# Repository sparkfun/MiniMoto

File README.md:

**NOTE:** *This product has been retired from our catalog. If you are looking for more up-to-date info, please check out some of these resources to see how other users are still hacking and improving on this product.*
* *[SparkFun Forum](https://forum.sparkfun.com/)*
* *[Comments Here on GitHub](https://github.com/sparkfun/MiniMoto/issues)*
* *[IRC Channel](https://www.sparkfun.com/news/263)*

SparkFun MiniMoto Breakout - DRV8830
=========================================

[*SparkFun MiniMoto Breakout - DRV8830(BOB-11890)*](https://www.sparkfun.com/products/11890)

The MiniMoto is a breakout board for the DRV8830 I<sup>2</sup>C DC motor driver. It operates between 2.7V to 6.8V

Repository Contents
-------------------
* **/Hardware** - All Eagle design files (.brd, .sch)
* **/Libraries** - All Arduino libraries and board examples
* **/Production** - Test bed files and production panel files

Documentation
--------------
* **[Library](https://github.com/sparkfun/SparkFun_MiniMoto_Arduino_Library)** - Arduinolibrary for the MiniMoto.
* **[Hookup Guide](https://learn.sparkfun.com/tutorials/minimoto-drv8830-hookup-guide)** - Basic hookup guide for the MiniMoto.
* **[SparkFun Fritzing repo](https://github.com/sparkfun/Fritzing_Parts)** - Fritzing diagrams for SparkFun products.
* **[SparkFun 3D Model repo](https://github.com/sparkfun/3D_Models)** - 3D models of SparkFun products. 

License Information
-------------------
This product is _**open source**_! 

The **hardware** is released under [Creative Commons ShareAlike 4.0 International](https://creativecommons.org/licenses/by-sa/4.0/).

The **code** is beerware; if you see me (or any other SparkFun employee) at the local, and you've found our code helpful, please buy us a round!

Please use, reuse, and modify these files as you see fit. Please maintain attribution to SparkFun Electronics and release anything derivative under the same license.

Distributed as-is; no warranty is given.

- Your friends at SparkFun.

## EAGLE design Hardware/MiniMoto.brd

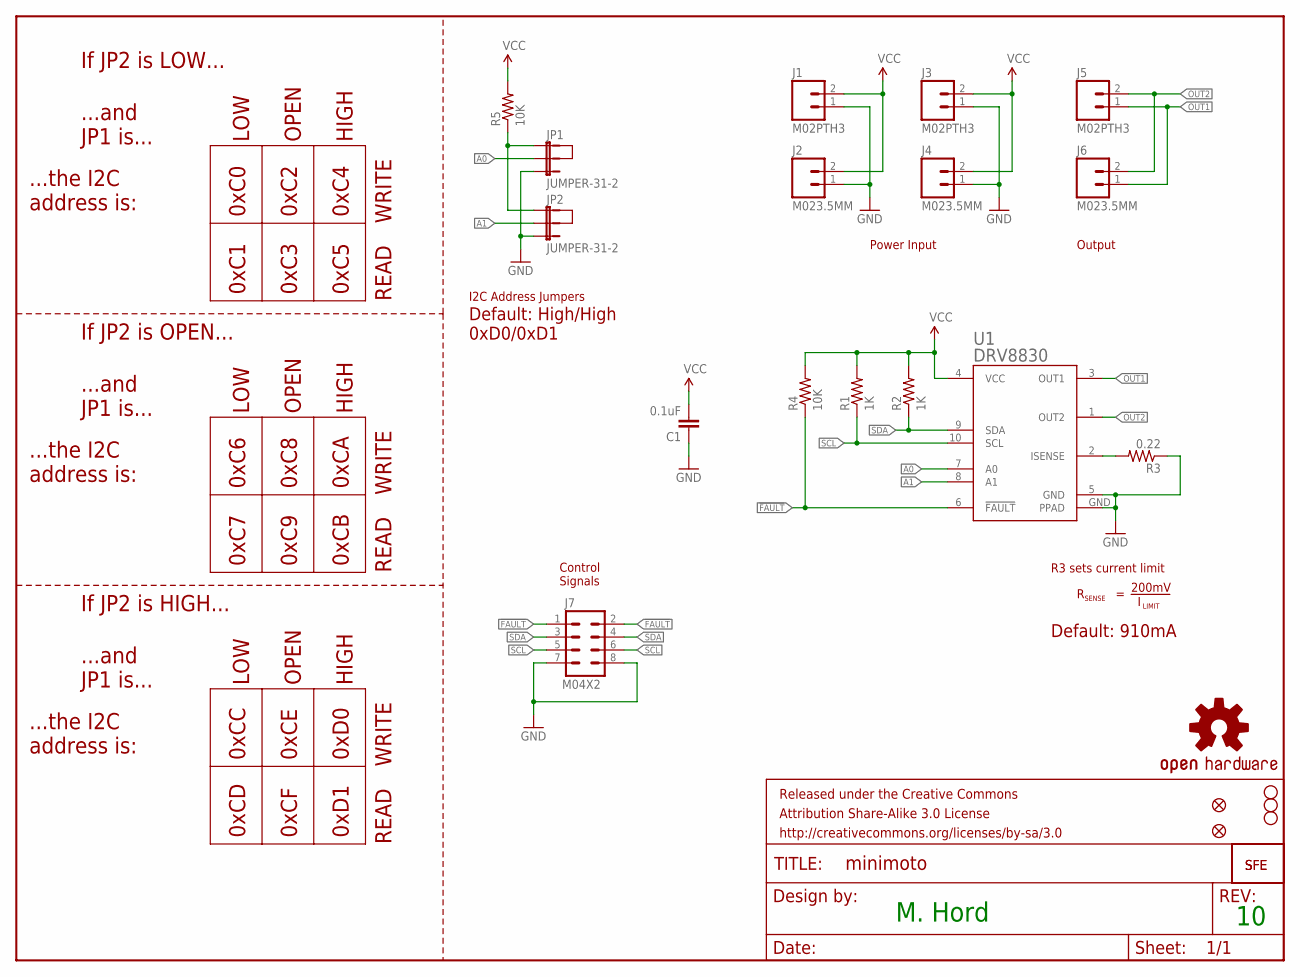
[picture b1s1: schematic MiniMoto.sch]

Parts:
C1: 0.1uF; 0603-CAP
FID1, FID2: FIDUCIALUFIDUCIAL; MICRO-FIDUCIAL
FRAME1: FRAME-LETTER; CREATIVE_COMMONS
J1, J3, J5: M02PTH3; 1X02_LONGPADS
J2, J4, J6: M023.5MM; SCREWTERMINAL-3.5MM-2
J7: M04X2; 2X4
JP1, JP2: JUMPER-31-2; SJ_3_PASTE1&2
LOGO1, LOGO3: LOGO-SFESK; SFE-LOGO-FLAME
LOGO2: OSHW-LOGOS; OSHW-LOGO-S
R1, R2: 1K; 0603-RES
R3: 0.22; 0805
R4, R5: 10K; 0603-RES
STANDOFF1, STANDOFF2, STANDOFF3: STAND-OFF
U1: DRV8830; MSOP-10-GNDPAD

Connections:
!FAULT: J7.1, J7.2, R4.1, U1.6 (!FAULT)
A0: JP1.2, U1.7 (A0)
A1: JP2.2, U1.8 (A1)
GND: C1.1, J1.1, J2.1, J3.1, J4.1, J7.7, J7.8, JP1.3, JP2.3, R3.1, U1.5 (GND), U1.GND (PPAD)
unnamed: JP1.1, JP2.1, R5.1
unnamed: R3.2, U1.2 (ISENSE)
OUT1: J5.1, J6.1, U1.3 (OUT1)
OUT2: J5.2, J6.2, U1.1 (OUT2)
SCL: J7.5, J7.6, R1.1, U1.10 (SCL)
SDA: J7.3, J7.4, R2.1, U1.9 (SDA)
VCC: C1.2, J1.2, J2.2, J3.2, J4.2, R1.2, R2.2, R4.2, R5.2, U1.4 (VCC)

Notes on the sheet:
M. Hord
If JP2 is LOW...
HIGH
LOW
OPEN
...and JP1 is...
...the I2C address is:
0xC0
0xC2
0xC4
0xC1
0xC3
0xC5
WRITE
READ
If JP2 is OPEN...
0xC6
0xC8
0xCA
0xC7
0xC9
0xCB
If JP2 is HIGH...
0xCC
0xCE
0xD0
0xCD
0xCF
0xD1
R3 sets current limit
SENSE
200mV
LIMIT
Control Signals
Power Input
Output
I2C Address Jumpers
Default: High/High 0xD0/0xD1
Default: 910mA

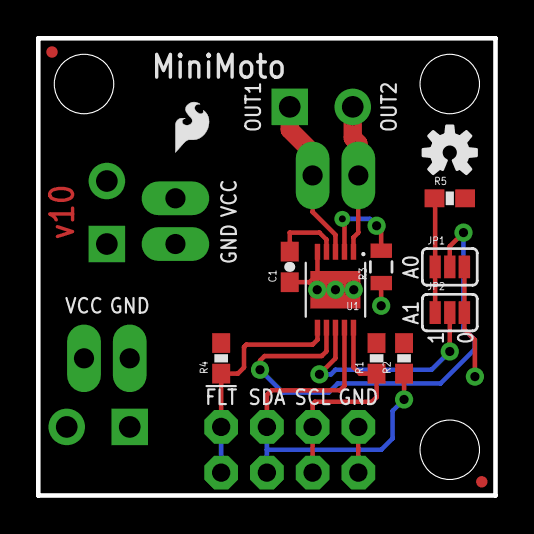
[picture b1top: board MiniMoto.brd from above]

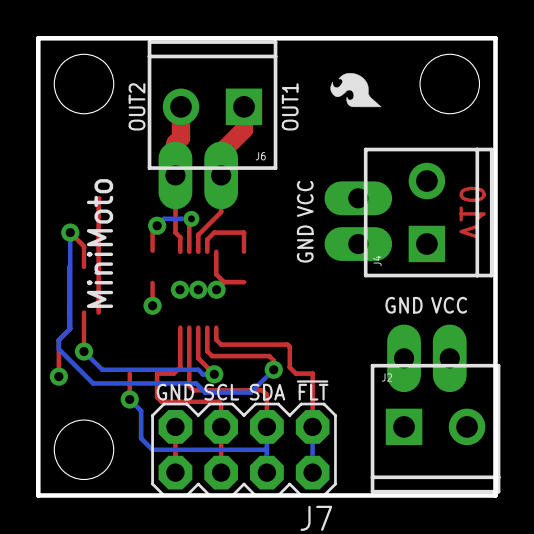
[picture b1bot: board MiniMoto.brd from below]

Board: 2 copper layers, 25.4 x 25.4 mm, 25 parts (7 on the bottom side), 11 nets.

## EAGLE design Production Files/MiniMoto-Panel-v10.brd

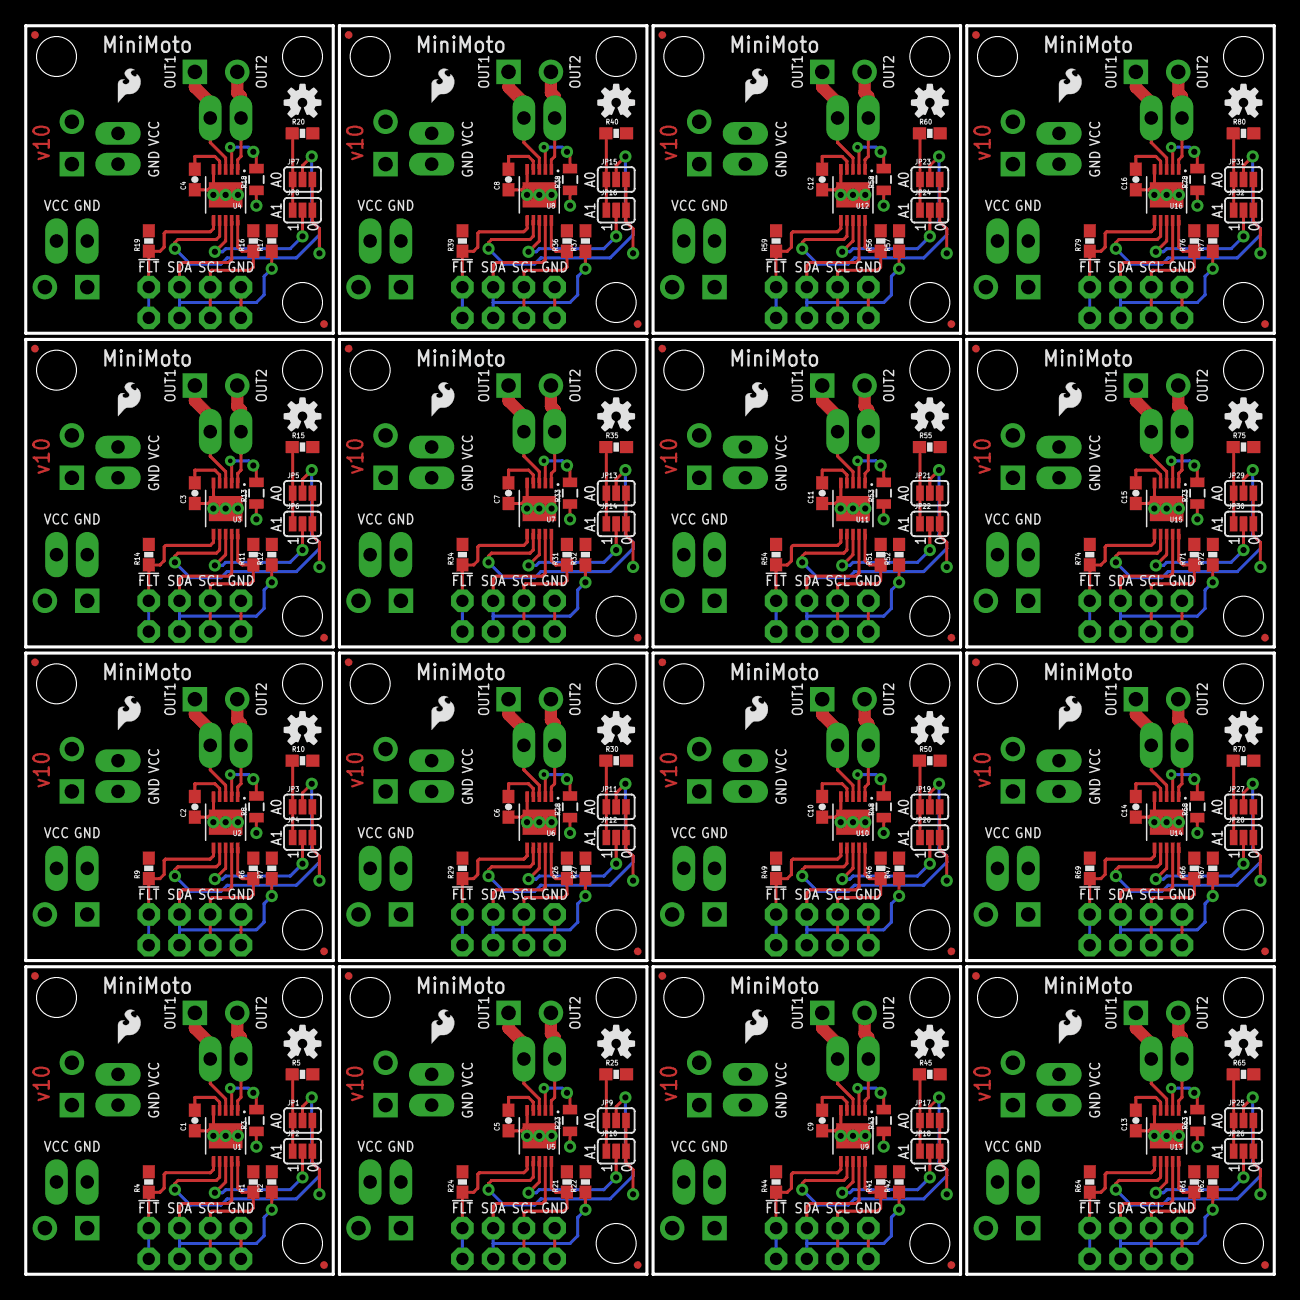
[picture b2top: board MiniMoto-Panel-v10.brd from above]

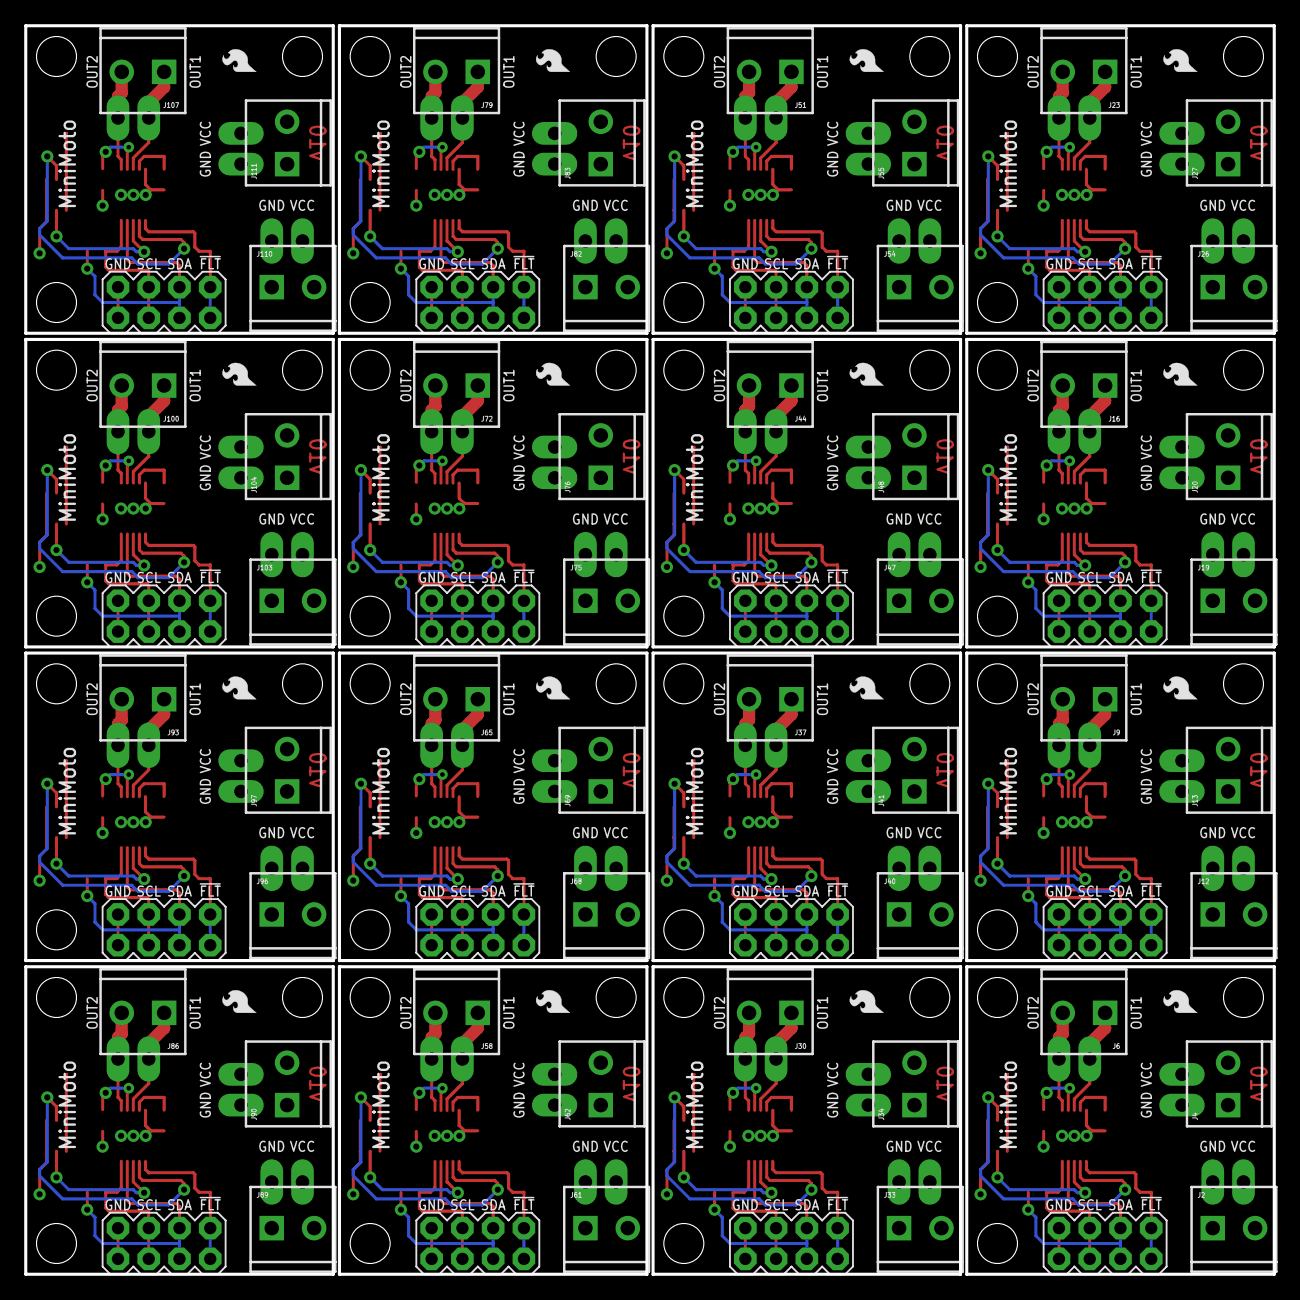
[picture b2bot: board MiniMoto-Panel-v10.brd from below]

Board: 2 copper layers, 103.1 x 103.1 mm, 384 parts (112 on the bottom side), 176 nets.

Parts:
C1, C2, C3, C4, C5, C6, C7, C8, C9, C10, C11, C12, C13, C14, C15, C16: 0.1uF; 0603-CAP
FID1, FID2, FID3, FID4, FID5, FID6, FID7, FID8, FID9, FID10, FID11, FID12, FID13, FID14, FID15, FID16, FID17, FID18, FID19, FID20, FID21, FID22, FID23, FID24, FID25, FID26, FID27, FID28, FID29, FID30, FID31, FID32: FIDUCIALUFIDUCIAL; MICRO-FIDUCIAL
J1, J3, J5, J8, J11, J14, J15, J18, J21, J22, J25, J28, J29, J32, J35, J36, J39, J42, J43, J46, J49, J50, J53, J56, J57, J60, J63, J64, J67, J70, J71, J74, J77, J78, J81, J84, J85, J88, J91, J92, J95, J98, J99, J102, J105, J106, J109, J112: M02PTH3; 1X02_LONGPADS
J2, J4, J6, J9, J12, J13, J16, J19, J20, J23, J26, J27, J30, J33, J34, J37, J40, J41, J44, J47, J48, J51, J54, J55, J58, J61, J62, J65, J68, J69, J72, J75, J76, J79, J82, J83, J86, J89, J90, J93, J96, J97, J100, J103, J104, J107, J110, J111: M023.5MM; SCREWTERMINAL-3.5MM-2
J7, J10, J17, J24, J31, J38, J45, J52, J59, J66, J73, J80, J87, J94, J101, J108: M04X2; 2X4
JP1, JP2, JP3, JP4, JP5, JP6, JP7, JP8, JP9, JP10, JP11, JP12, JP13, JP14, JP15, JP16, JP17, JP18, JP19, JP20, JP21, JP22, JP23, JP24, JP25, JP26, JP27, JP28, JP29, JP30, JP31, JP32: JUMPER-31-2; SJ_3_PASTE1&2
LOGO1, LOGO3, LOGO5, LOGO6, LOGO8, LOGO9, LOGO11, LOGO12, LOGO14, LOGO15, LOGO17, LOGO18, LOGO20, LOGO21, LOGO23, LOGO24, LOGO26, LOGO27, LOGO29, LOGO30, LOGO32, LOGO33, LOGO35, LOGO36, LOGO38, LOGO39, LOGO41, LOGO42, LOGO44, LOGO45, LOGO47, LOGO48: LOGO-SFESK; SFE-LOGO-FLAME
LOGO2, LOGO4, LOGO7, LOGO10, LOGO13, LOGO16, LOGO19, LOGO22, LOGO25, LOGO28, LOGO31, LOGO34, LOGO37, LOGO40, LOGO43, LOGO46: OSHW-LOGOS; OSHW-LOGO-S
R1, R2, R6, R7, R11, R12, R16, R17, R21, R22, R26, R27, R31, R32, R36, R37, R41, R42, R46, R47, R51, R52, R56, R57, R61, R62, R66, R67, R71, R72, R76, R77: 1K; 0603-RES
R3, R8, R13, R18, R23, R28, R33, R38, R43, R48, R53, R58, R63, R68, R73, R78: 0.22; 0805
R4, R5, R9, R10, R14, R15, R19, R20, R24, R25, R29, R30, R34, R35, R39, R40, R44, R45, R49, R50, R54, R55, R59, R60, R64, R65, R69, R70, R74, R75, R79, R80: 10K; 0603-RES
STANDOFF1, STANDOFF2, STANDOFF3, STANDOFF4, STANDOFF5, STANDOFF6, STANDOFF7, STANDOFF8, STANDOFF9, STANDOFF10, STANDOFF11, STANDOFF12, STANDOFF13, STANDOFF14, STANDOFF15, STANDOFF16, STANDOFF17, STANDOFF18, STANDOFF19, STANDOFF20, STANDOFF21, STANDOFF22, STANDOFF23, STANDOFF24, STANDOFF25, STANDOFF26, STANDOFF27, STANDOFF28, STANDOFF29, STANDOFF30, STANDOFF31, STANDOFF32, STANDOFF33, STANDOFF34, STANDOFF35, STANDOFF36, STANDOFF37, STANDOFF38, STANDOFF39, STANDOFF40, STANDOFF41, STANDOFF42, STANDOFF43, STANDOFF44, STANDOFF45, STANDOFF46, STANDOFF47, STANDOFF48: STAND-OFF
U1, U2, U3, U4, U5, U6, U7, U8, U9, U10, U11, U12, U13, U14, U15, U16: DRV8830; MSOP-10-GNDPAD

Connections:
!FAULT: J7.1, J7.2, R4.1, U1.6
!FAULT1: J10.1, J10.2, R9.1, U2.6
!FAULT2: J17.1, J17.2, R14.1, U3.6
!FAULT3: J24.1, J24.2, R19.1, U4.6
!FAULT4: J31.1, J31.2, R24.1, U5.6
!FAULT5: J38.1, J38.2, R29.1, U6.6
!FAULT6: J45.1, J45.2, R34.1, U7.6
!FAULT7: J52.1, J52.2, R39.1, U8.6
!FAULT8: J59.1, J59.2, R44.1, U9.6
!FAULT9: J66.1, J66.2, R49.1, U10.6
!FAULT10: J73.1, J73.2, R54.1, U11.6
!FAULT11: J80.1, J80.2, R59.1, U12.6
!FAULT12: J87.1, J87.2, R64.1, U13.6
!FAULT13: J94.1, J94.2, R69.1, U14.6
!FAULT14: J101.1, J101.2, R74.1, U15.6
!FAULT15: J108.1, J108.2, R79.1, U16.6
A0: JP1.2, U1.7
A1: JP2.2, U1.8
A2: JP3.2, U2.7
A3: JP4.2, U2.8
A4: JP5.2, U3.7
A5: JP6.2, U3.8
A6: JP7.2, U4.7
A7: JP8.2, U4.8
A8: JP9.2, U5.7
A9: JP10.2, U5.8
A10: JP11.2, U6.7
A11: JP12.2, U6.8
A12: JP13.2, U7.7
A13: JP14.2, U7.8
A14: JP15.2, U8.7
A15: JP16.2, U8.8
A16: JP17.2, U9.7
A17: JP18.2, U9.8
A18: JP19.2, U10.7
A19: JP20.2, U10.8
A20: JP21.2, U11.7
A21: JP22.2, U11.8
A22: JP23.2, U12.7
A23: JP24.2, U12.8
A24: JP25.2, U13.7
A25: JP26.2, U13.8
A26: JP27.2, U14.7
A27: JP28.2, U14.8
A28: JP29.2, U15.7
A29: JP30.2, U15.8
A30: JP31.2, U16.7
A31: JP32.2, U16.8
GND: C1.1, J1.1, J2.1, J3.1, J4.1, J7.7, J7.8, JP1.3, JP2.3, R3.1, U1.5, U1.GND
GND1: C2.1, J10.7, J10.8, J11.1, J12.1, J13.1, J14.1, JP3.3, JP4.3, R8.1, U2.5, U2.GND
GND2: C3.1, J17.7, J17.8, J18.1, J19.1, J20.1, J21.1, JP5.3, JP6.3, R13.1, U3.5, U3.GND
GND3: C4.1, J24.7, J24.8, J25.1, J26.1, J27.1, J28.1, JP7.3, JP8.3, R18.1, U4.5, U4.GND
GND4: C5.1, J31.7, J31.8, J32.1, J33.1, J34.1, J35.1, JP9.3, JP10.3, R23.1, U5.5, U5.GND
GND5: C6.1, J38.7, J38.8, J39.1, J40.1, J41.1, J42.1, JP11.3, JP12.3, R28.1, U6.5, U6.GND
GND6: C7.1, J45.7, J45.8, J46.1, J47.1, J48.1, J49.1, JP13.3, JP14.3, R33.1, U7.5, U7.GND
GND7: C8.1, J52.7, J52.8, J53.1, J54.1, J55.1, J56.1, JP15.3, JP16.3, R38.1, U8.5, U8.GND
GND8: C9.1, J59.7, J59.8, J60.1, J61.1, J62.1, J63.1, JP17.3, JP18.3, R43.1, U9.5, U9.GND
GND9: C10.1, J66.7, J66.8, J67.1, J68.1, J69.1, J70.1, JP19.3, JP20.3, R48.1, U10.5, U10.GND
GND10: C11.1, J73.7, J73.8, J74.1, J75.1, J76.1, J77.1, JP21.3, JP22.3, R53.1, U11.5, U11.GND
GND11: C12.1, J80.7, J80.8, J81.1, J82.1, J83.1, J84.1, JP23.3, JP24.3, R58.1, U12.5, U12.GND
GND12: C13.1, J87.7, J87.8, J88.1, J89.1, J90.1, J91.1, JP25.3, JP26.3, R63.1, U13.5, U13.GND
GND13: C14.1, J94.7, J94.8, J95.1, J96.1, J97.1, J98.1, JP27.3, JP28.3, R68.1, U14.5, U14.GND
GND14: C15.1, J101.7, J101.8, J102.1, J103.1, J104.1, J105.1, JP29.3, JP30.3, R73.1, U15.5, U15.GND
GND15: C16.1, J108.7, J108.8, J109.1, J110.1, J111.1, J112.1, JP31.3, JP32.3, R78.1, U16.5, U16.GND
unnamed: JP1.1, JP2.1, R5.1
unnamed: R8.2, U2.2
unnamed: R3.2, U1.2
unnamed: JP3.1, JP4.1, R10.1
unnamed: R13.2, U3.2
unnamed: JP5.1, JP6.1, R15.1
unnamed: R18.2, U4.2
unnamed: JP7.1, JP8.1, R20.1
unnamed: R23.2, U5.2
unnamed: JP9.1, JP10.1, R25.1
unnamed: R28.2, U6.2
unnamed: JP11.1, JP12.1, R30.1
unnamed: R33.2, U7.2
unnamed: JP13.1, JP14.1, R35.1
unnamed: R38.2, U8.2
unnamed: JP15.1, JP16.1, R40.1
unnamed: R43.2, U9.2
unnamed: JP17.1, JP18.1, R45.1
unnamed: R48.2, U10.2
unnamed: JP19.1, JP20.1, R50.1
unnamed: R53.2, U11.2
unnamed: JP21.1, JP22.1, R55.1
unnamed: R58.2, U12.2
unnamed: JP23.1, JP24.1, R60.1
unnamed: R63.2, U13.2
unnamed: JP25.1, JP26.1, R65.1
unnamed: R68.2, U14.2
unnamed: JP27.1, JP28.1, R70.1
unnamed: R73.2, U15.2
unnamed: JP29.1, JP30.1, R75.1
unnamed: R78.2, U16.2
unnamed: JP31.1, JP32.1, R80.1
OUT1: J5.1, J6.1, U1.3
OUT2: J5.2, J6.2, U1.1
OUT3: J8.1, J9.1, U2.3
OUT4: J8.2, J9.2, U2.1
OUT5: J15.1, J16.1, U3.3
OUT6: J15.2, J16.2, U3.1
OUT7: J22.1, J23.1, U4.3
OUT8: J22.2, J23.2, U4.1
OUT9: J29.1, J30.1, U5.3
OUT10: J29.2, J30.2, U5.1
OUT11: J36.1, J37.1, U6.3
OUT12: J36.2, J37.2, U6.1
OUT13: J43.1, J44.1, U7.3
OUT14: J43.2, J44.2, U7.1
OUT15: J50.1, J51.1, U8.3
OUT16: J50.2, J51.2, U8.1
OUT17: J57.1, J58.1, U9.3
OUT18: J57.2, J58.2, U9.1
OUT19: J64.1, J65.1, U10.3
OUT20: J64.2, J65.2, U10.1
OUT21: J71.1, J72.1, U11.3
OUT22: J71.2, J72.2, U11.1
OUT23: J78.1, J79.1, U12.3
OUT24: J78.2, J79.2, U12.1
OUT25: J85.1, J86.1, U13.3
OUT26: J85.2, J86.2, U13.1
OUT27: J92.1, J93.1, U14.3
OUT28: J92.2, J93.2, U14.1
OUT29: J99.1, J100.1, U15.3
OUT30: J99.2, J100.2, U15.1
OUT31: J106.1, J107.1, U16.3
OUT32: J106.2, J107.2, U16.1
SCL: J7.5, J7.6, R1.1, U1.10
SCL1: J10.5, J10.6, R6.1, U2.10
SCL2: J17.5, J17.6, R11.1, U3.10
SCL3: J24.5, J24.6, R16.1, U4.10
SCL4: J31.5, J31.6, R21.1, U5.10
SCL5: J38.5, J38.6, R26.1, U6.10
SCL6: J45.5, J45.6, R31.1, U7.10
SCL7: J52.5, J52.6, R36.1, U8.10
SCL8: J59.5, J59.6, R41.1, U9.10
SCL9: J66.5, J66.6, R46.1, U10.10
SCL10: J73.5, J73.6, R51.1, U11.10
SCL11: J80.5, J80.6, R56.1, U12.10
SCL12: J87.5, J87.6, R61.1, U13.10
SCL13: J94.5, J94.6, R66.1, U14.10
SCL14: J101.5, J101.6, R71.1, U15.10
SCL15: J108.5, J108.6, R76.1, U16.10
SDA: J7.3, J7.4, R2.1, U1.9
SDA1: J10.3, J10.4, R7.1, U2.9
SDA2: J17.3, J17.4, R12.1, U3.9
SDA3: J24.3, J24.4, R17.1, U4.9
SDA4: J31.3, J31.4, R22.1, U5.9
SDA5: J38.3, J38.4, R27.1, U6.9
SDA6: J45.3, J45.4, R32.1, U7.9
SDA7: J52.3, J52.4, R37.1, U8.9
SDA8: J59.3, J59.4, R42.1, U9.9
SDA9: J66.3, J66.4, R47.1, U10.9
SDA10: J73.3, J73.4, R52.1, U11.9
SDA11: J80.3, J80.4, R57.1, U12.9
SDA12: J87.3, J87.4, R62.1, U13.9
SDA13: J94.3, J94.4, R67.1, U14.9
SDA14: J101.3, J101.4, R72.1, U15.9
SDA15: J108.3, J108.4, R77.1, U16.9
VCC: C1.2, J1.2, J2.2, J3.2, J4.2, R1.2, R2.2, R4.2, R5.2, U1.4
VCC1: C2.2, J11.2, J12.2, J13.2, J14.2, R6.2, R7.2, R9.2, R10.2, U2.4
VCC2: C3.2, J18.2, J19.2, J20.2, J21.2, R11.2, R12.2, R14.2, R15.2, U3.4
VCC3: C4.2, J25.2, J26.2, J27.2, J28.2, R16.2, R17.2, R19.2, R20.2, U4.4
VCC4: C5.2, J32.2, J33.2, J34.2, J35.2, R21.2, R22.2, R24.2, R25.2, U5.4
VCC5: C6.2, J39.2, J40.2, J41.2, J42.2, R26.2, R27.2, R29.2, R30.2, U6.4
VCC6: C7.2, J46.2, J47.2, J48.2, J49.2, R31.2, R32.2, R34.2, R35.2, U7.4
VCC7: C8.2, J53.2, J54.2, J55.2, J56.2, R36.2, R37.2, R39.2, R40.2, U8.4
VCC8: C9.2, J60.2, J61.2, J62.2, J63.2, R41.2, R42.2, R44.2, R45.2, U9.4
VCC9: C10.2, J67.2, J68.2, J69.2, J70.2, R46.2, R47.2, R49.2, R50.2, U10.4
VCC10: C11.2, J74.2, J75.2, J76.2, J77.2, R51.2, R52.2, R54.2, R55.2, U11.4
VCC11: C12.2, J81.2, J82.2, J83.2, J84.2, R56.2, R57.2, R59.2, R60.2, U12.4
VCC12: C13.2, J88.2, J89.2, J90.2, J91.2, R61.2, R62.2, R64.2, R65.2, U13.4
VCC13: C14.2, J95.2, J96.2, J97.2, J98.2, R66.2, R67.2, R69.2, R70.2, U14.4
VCC14: C15.2, J102.2, J103.2, J104.2, J105.2, R71.2, R72.2, R74.2, R75.2, U15.4
VCC15: C16.2, J109.2, J110.2, J111.2, J112.2, R76.2, R77.2, R79.2, R80.2, U16.4

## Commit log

2013-06-03 Initial commit for protos
2013-07-16 Tweaks for release, add lib
2013-07-16 Tweaks to library files
2013-07-24 Updated to v10 for release
2013-07-25 Production Readied
2013-09-10 Reorganized Arduino folder. Moved example into library folder.
2013-09-10 Moved example into Arduino library folder.
2013-09-17 Adding Arduino Library and example code.
2013-11-14 Updating README
2013-12-28 Changed library to work with Arduino Wire lib
    Modified library to work with built-in Wire.h. This should make the
    library a bit more cross-platform compatible.
2014-05-23 Move library to Arduino folder, line endings
2014-05-23 Revert "Move library to Arduino folder, line endings"
    This reverts commit 295bfce20a394f6c63947fa651fac41841a54c73.
2014-05-23 Move "Libraries" into "Arduino".
    I hosed this before, or rather, bash did. I'm trying to figure out how.
2014-05-23 Man, I'm not on my game.
2014-12-31 Adding in library changes from customer Ed Wilson
2015-05-15 Updating directory structure, updating readmes
2015-05-15 Squashed 'Libraries/Arduino/' content from commit 1b42fbb
    git-subtree-dir: Libraries/Arduino
    git-subtree-split: 1b42fbbbe25c134150f8e9cb268108fa5aeeab93

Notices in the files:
parts and their libraries:
SparkFun-Aesthetics: Licensing: CC v3.0 Share-Alike You are welcome to use this library for commercial purposes.
SparkFun-Aesthetics: Released under the Creative Commons Attribution Share-Alike 3.0 License
SparkFun-Aesthetics: http://creativecommons.org/licenses/by-sa/3.0
